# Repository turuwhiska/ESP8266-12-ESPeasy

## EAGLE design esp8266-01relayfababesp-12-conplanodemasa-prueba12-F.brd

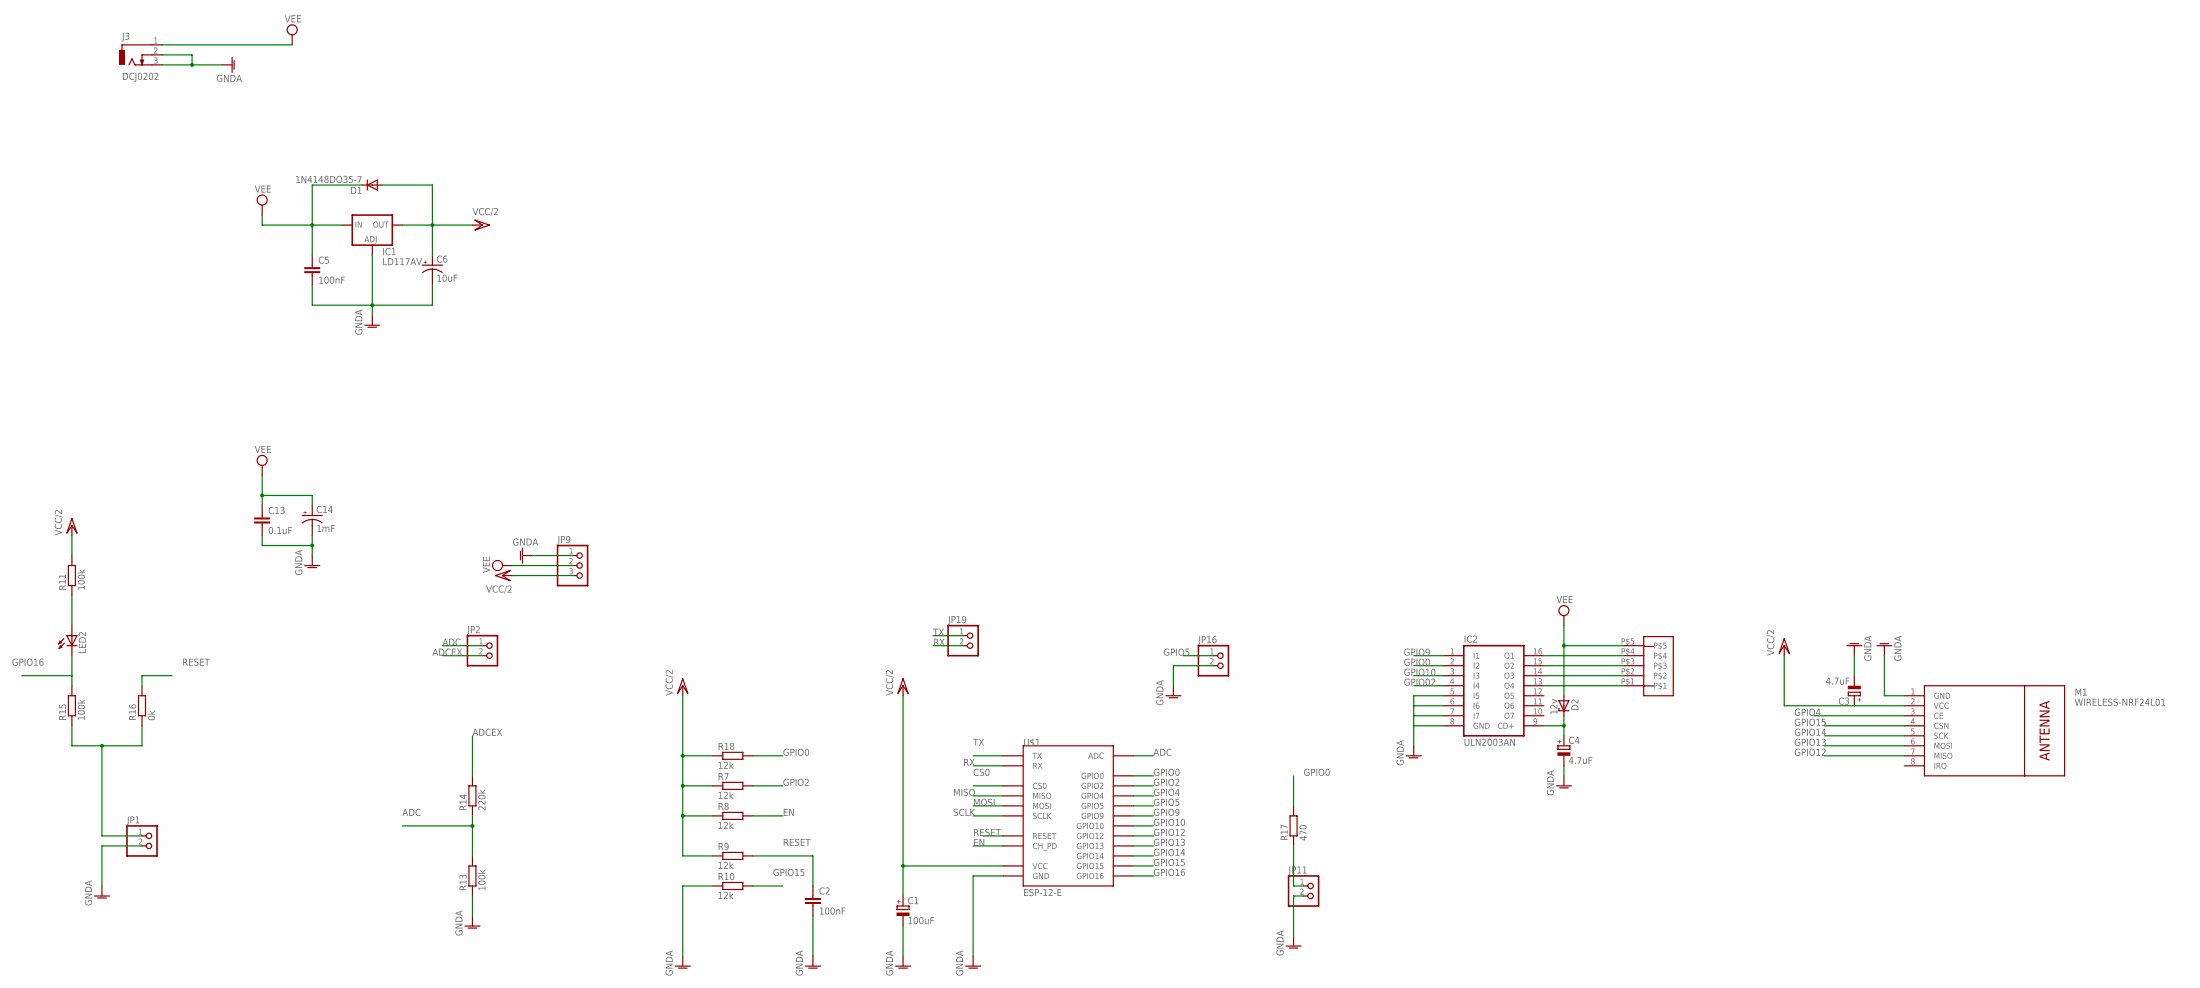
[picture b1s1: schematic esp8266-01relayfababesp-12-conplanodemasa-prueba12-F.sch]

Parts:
C1: 100uF; TT5D7
C2: 100nF; C025-024X044
C3, C4: 4.7uF; TT5D7
C5: 100nF; C025-025X050
C6: 10uF; E2,5-6E
C13: 0.1uF; C025-025X050
C14: 1mF; E2,5-6E
D1: 1N4148DO35-7; DO35-7
D2: 12v; P1Z12
IC1: LD117AV; TO220L1
IC2: ULN2003AN; DIL16
J3: DCJ0202
JP1, JP2, JP11, JP16, JP19: PINHD-1X2; 1X02
JP9: PINHD-1X3; 1X03
LED2: LED3MM
M1: WIRELESS-NRF24L01
R7, R8, R9, R10, R18: 12k; 0207/7
R11, R13, R15: 100k; 0207/7
R14: 220k; 0207/7
R16: 0k; 0207/7
R17: 470; 0207/7
U$1: ESP-12-E
U$3: 5_PIN_JST-XH

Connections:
ADC: JP2.1, R13.2, R14.1, U$1.ADC
ADCEX: JP2.2, R14.2
CS0: U$1.CS0
EN: R8.2, U$1.CH_PD
GNDA: C1.-, C2.2, C3.-, C4.-, C5.2, C6.-, C13.2, C14.-, IC1.1 (ADJ), IC2.5 (I5), IC2.6 (I6), IC2.7 (I7), IC2.8 (GND), J3.2, J3.3, JP1.2, JP9.1, JP11.2, JP16.2, M1.1 (GND), R10.1, R13.1, U$1.GND
GPIO0: IC2.2 (I2), R17.2, R18.2, U$1.GPIO0
GPIO2: R7.2, U$1.GPIO2
GPIO02: IC2.4 (I4)
GPIO4: M1.3 (CE), U$1.GPIO4
GPIO5: JP16.1, U$1.GPIO5
GPIO9: IC2.1 (I1), U$1.GPIO9
GPIO10: IC2.3 (I3), U$1.GPIO10
GPIO12: M1.7 (MISO), U$1.GPIO12
GPIO13: M1.6 (MOSI), U$1.GPIO13
GPIO14: M1.5 (SCK), U$1.GPIO14
GPIO15: M1.4 (CSN), R10.2, U$1.GPIO15
GPIO16: LED2.K (C), R15.2, U$1.GPIO16
MISO: U$1.MISO
MOSI: U$1.MOSI
unnamed: IC2.16 (O1), U$3.P$4
unnamed: IC2.15 (O2), U$3.P$3
unnamed: IC2.14 (O3), U$3.P$2
unnamed: JP11.1, R17.1
unnamed: IC2.13 (O4), U$3.P$1
unnamed: LED2.A, R11.1
unnamed: C4.+, D2.C, IC2.9 (CD+)
unnamed: JP1.1, R15.1, R16.1
RESET: C2.1, R9.2, R16.2, U$1.RESET
RX: JP19.2, U$1.RX
SCLK: U$1.SCLK
TX: JP19.1, U$1.TX
VCC/2: C1.+, C3.+, C6.+, D1.A, IC1.2 (OUT), JP9.3, M1.2 (VCC), R7.1, R8.1, R9.1, R11.2, R18.1, U$1.VCC
VEE: C5.1, C13.1, C14.+, D1.C, D2.A, IC1.3 (IN), J3.1, JP9.2, U$3.P$5

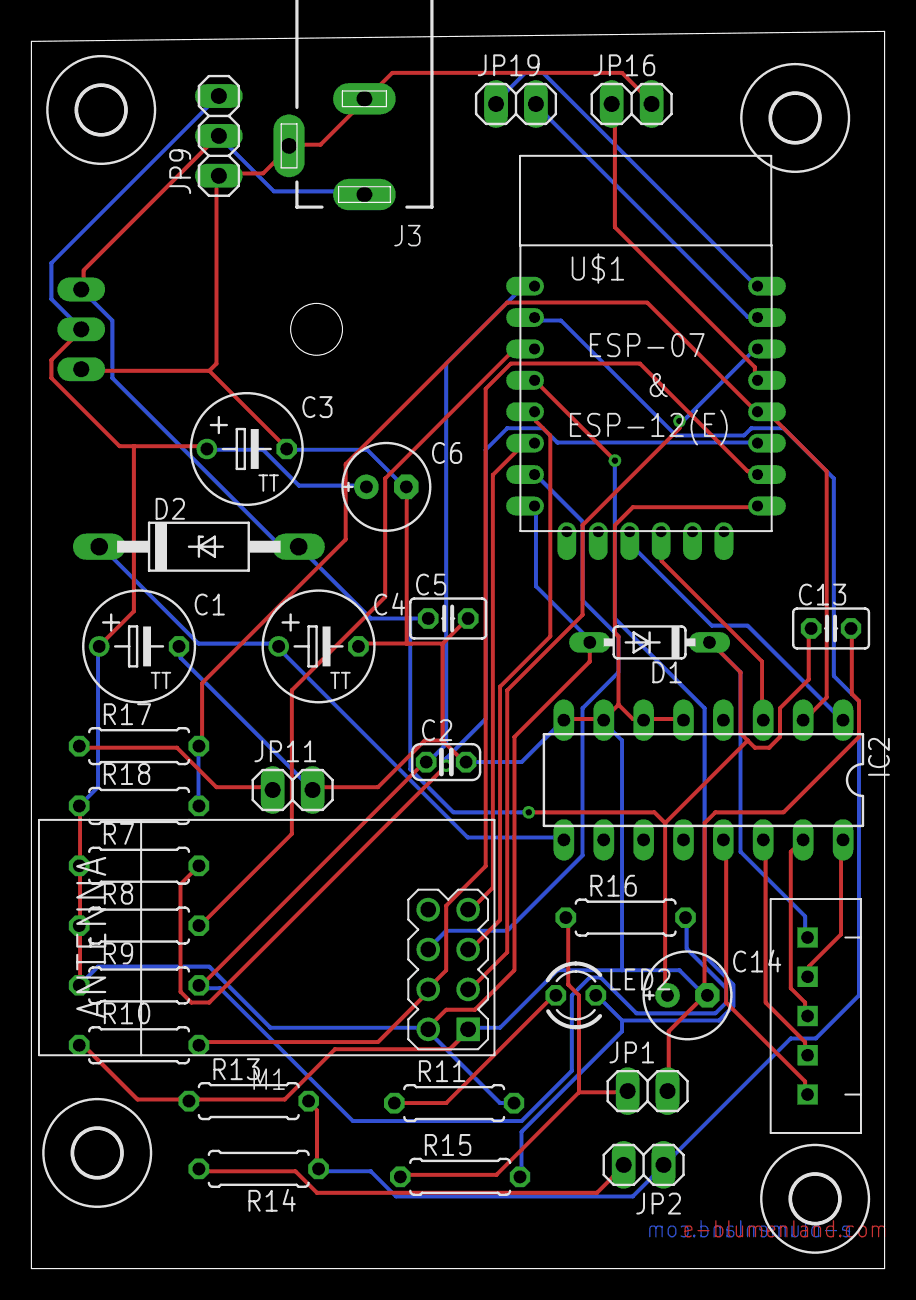
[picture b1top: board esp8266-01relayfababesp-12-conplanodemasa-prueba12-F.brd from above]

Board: 2 copper layers, 54.3 x 78.8 mm, 38 parts (1 on the bottom side), 28 nets.

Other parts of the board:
H1, H2, H7, H8: MOUNT-HOLE3.0; 3,0

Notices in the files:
parts and their libraries:
diy-modules: Released under the Creative Commons Attribution 4.0 International License: http://creativecommons.org/licenses/by/4.0
